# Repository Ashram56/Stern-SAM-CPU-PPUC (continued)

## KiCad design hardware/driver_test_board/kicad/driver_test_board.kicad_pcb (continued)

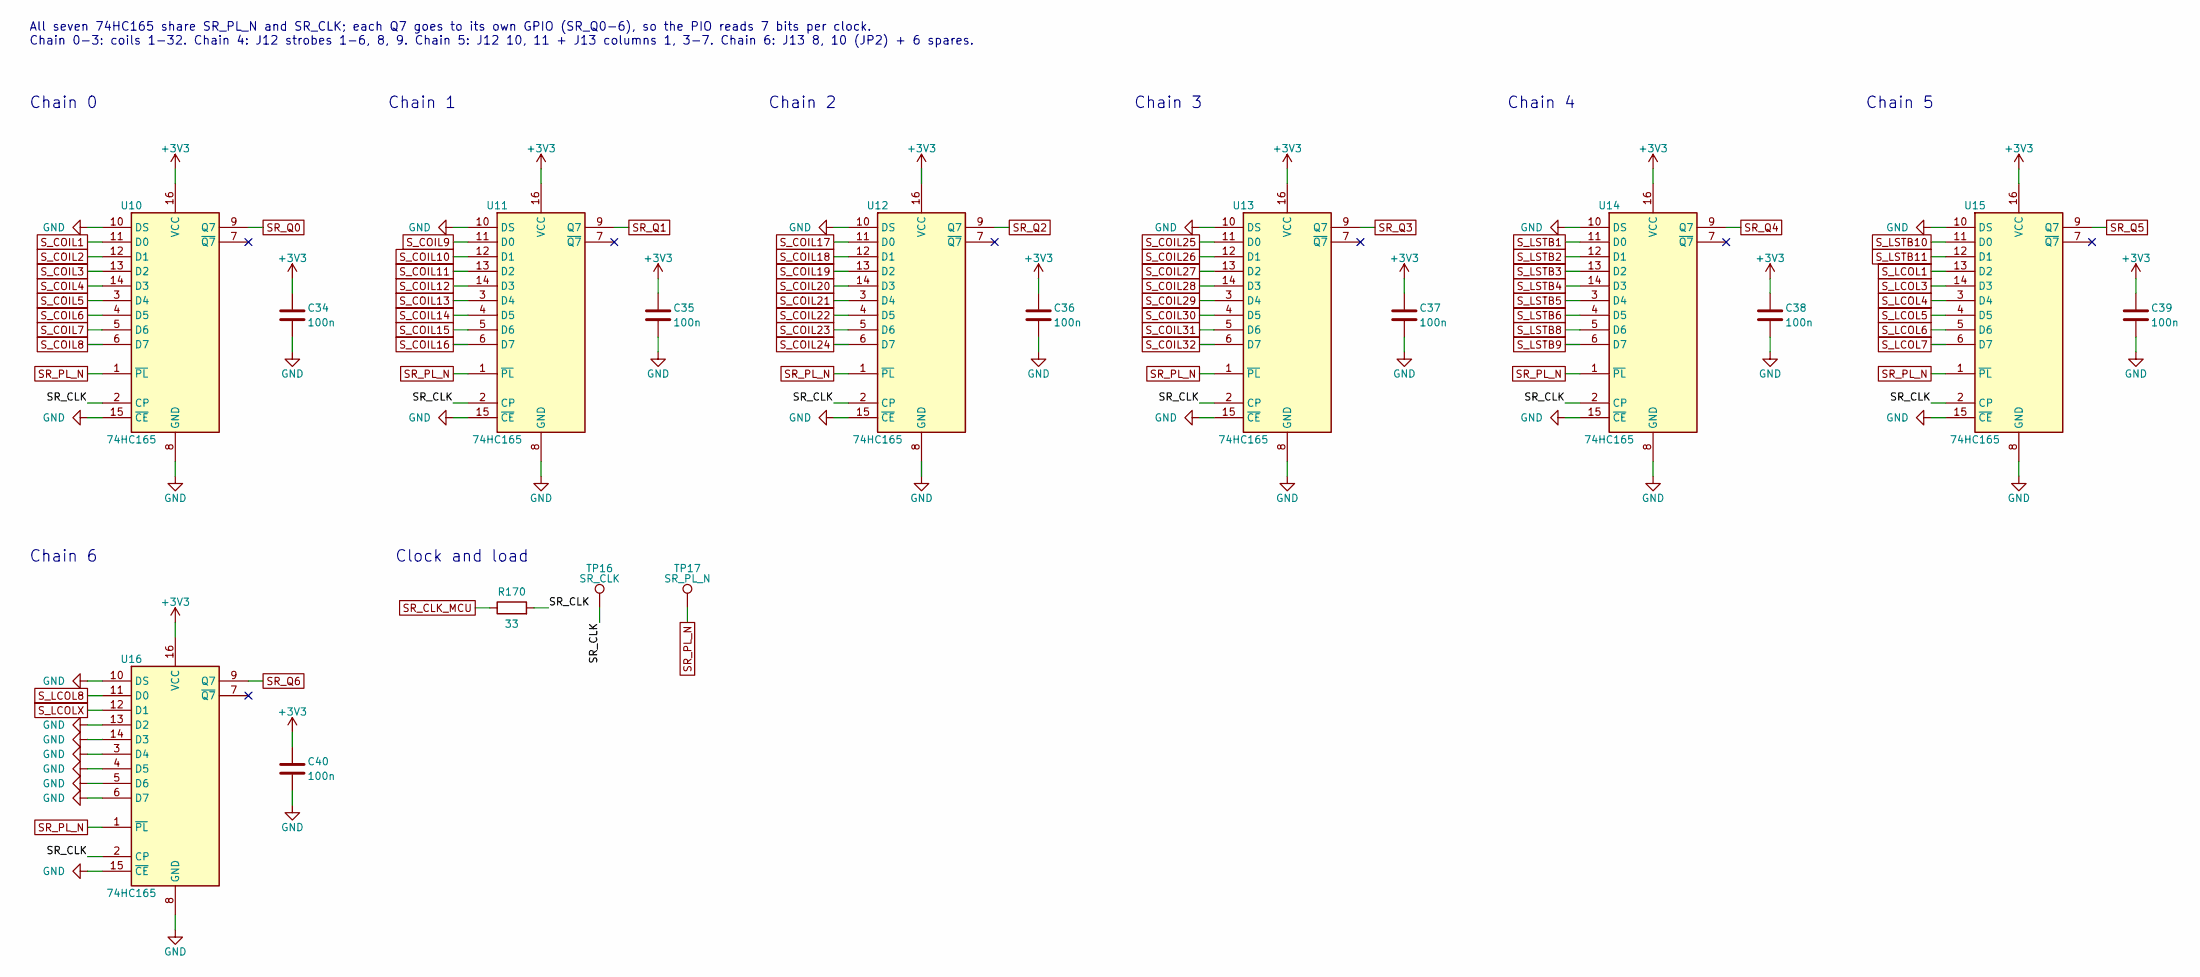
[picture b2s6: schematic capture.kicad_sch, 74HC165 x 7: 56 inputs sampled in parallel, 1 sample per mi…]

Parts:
C34, C35, C36, C37, C38, C39, C40: 100n; C_0805_2012Metric
R170: 33; R_0805_2012Metric
TP16: SR_CLK; TestPoint_Pad_D1.5mm
TP17: SR_PL_N; TestPoint_Pad_D1.5mm
U10, U11, U12, U13, U14, U15, U16: 74HC165; SOIC-16_3.9x9.9mm_P1.27mm

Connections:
+3V3: C34.1, C35.1, C36.1, C37.1, C38.1, C39.1, C40.1, U10.16 (VCC), U11.16 (VCC), U12.16 (VCC), U13.16 (VCC), U14.16 (VCC), U15.16 (VCC), U16.16 (VCC); also elsewhere on the board
/Capture/SR_CLK: R170.2, TP16.1, U10.2 (CP), U11.2 (CP), U12.2 (CP), U13.2 (CP), U14.2 (CP), U15.2 (CP), U16.2 (CP)
GND: C34.2, C35.2, C36.2, C37.2, C38.2, C39.2, C40.2, U10.8 (GND), U10.10 (DS), U10.15 (~CE), U11.8 (GND), U11.10 (DS), U11.15 (~CE), U12.8 (GND), U12.10 (DS), U12.15 (~CE), U13.8 (GND), U13.10 (DS), U13.15 (~CE), U14.8 (GND), U14.10 (DS), U14.15 (~CE), U15.8 (GND), U15.10 (DS), U15.15 (~CE), U16.3 (D4), U16.4 (D5), U16.5 (D6), U16.6 (D7), U16.8 (GND), U16.10 (DS), U16.13 (D2), U16.14 (D3), U16.15 (~CE); also elsewhere on the board
SR_CLK_MCU: R170.1; also elsewhere on the board
SR_PL_N: TP17.1, U10.1 (~PL), U11.1 (~PL), U12.1 (~PL), U13.1 (~PL), U14.1 (~PL), U15.1 (~PL), U16.1 (~PL); also elsewhere on the board
SR_Q0: U10.9 (Q7); also elsewhere on the board
SR_Q1: U11.9 (Q7); also elsewhere on the board
SR_Q2: U12.9 (Q7); also elsewhere on the board
SR_Q3: U13.9 (Q7); also elsewhere on the board
SR_Q4: U14.9 (Q7); also elsewhere on the board
SR_Q5: U15.9 (Q7); also elsewhere on the board
SR_Q6: U16.9 (Q7); also elsewhere on the board
S_COIL1: U10.11 (D0); also elsewhere on the board
S_COIL2: U10.12 (D1); also elsewhere on the board
S_COIL3: U10.13 (D2); also elsewhere on the board
S_COIL4: U10.14 (D3); also elsewhere on the board
S_COIL5: U10.3 (D4); also elsewhere on the board
S_COIL6: U10.4 (D5); also elsewhere on the board
S_COIL7: U10.5 (D6); also elsewhere on the board
S_COIL8: U10.6 (D7); also elsewhere on the board
S_COIL9: U11.11 (D0); also elsewhere on the board
S_COIL10: U11.12 (D1); also elsewhere on the board
S_COIL11: U11.13 (D2); also elsewhere on the board
S_COIL12: U11.14 (D3); also elsewhere on the board
S_COIL13: U11.3 (D4); also elsewhere on the board
S_COIL14: U11.4 (D5); also elsewhere on the board
S_COIL15: U11.5 (D6); also elsewhere on the board
S_COIL16: U11.6 (D7); also elsewhere on the board
S_COIL17: U12.11 (D0); also elsewhere on the board
S_COIL18: U12.12 (D1); also elsewhere on the board
S_COIL19: U12.13 (D2); also elsewhere on the board
S_COIL20: U12.14 (D3); also elsewhere on the board
S_COIL21: U12.3 (D4); also elsewhere on the board
S_COIL22: U12.4 (D5); also elsewhere on the board
S_COIL23: U12.5 (D6); also elsewhere on the board
S_COIL24: U12.6 (D7); also elsewhere on the board
S_COIL25: U13.11 (D0); also elsewhere on the board
S_COIL26: U13.12 (D1); also elsewhere on the board
S_COIL27: U13.13 (D2); also elsewhere on the board
S_COIL28: U13.14 (D3); also elsewhere on the board
S_COIL29: U13.3 (D4); also elsewhere on the board
S_COIL30: U13.4 (D5); also elsewhere on the board
S_COIL31: U13.5 (D6); also elsewhere on the board
S_COIL32: U13.6 (D7); also elsewhere on the board
S_LCOL1: U15.13 (D2); also elsewhere on the board
S_LCOL3: U15.14 (D3); also elsewhere on the board
S_LCOL4: U15.3 (D4); also elsewhere on the board
S_LCOL5: U15.4 (D5); also elsewhere on the board
S_LCOL6: U15.5 (D6); also elsewhere on the board
S_LCOL7: U15.6 (D7); also elsewhere on the board
S_LCOL8: U16.11 (D0); also elsewhere on the board
S_LCOLX: U16.12 (D1); also elsewhere on the board
S_LSTB1: U14.11 (D0); also elsewhere on the board
S_LSTB2: U14.12 (D1); also elsewhere on the board
S_LSTB3: U14.13 (D2); also elsewhere on the board
S_LSTB4: U14.14 (D3); also elsewhere on the board
S_LSTB5: U14.3 (D4); also elsewhere on the board
S_LSTB6: U14.4 (D5); also elsewhere on the board
S_LSTB8: U14.5 (D6); also elsewhere on the board
S_LSTB9: U14.6 (D7); also elsewhere on the board
S_LSTB10: U15.11 (D0); also elsewhere on the board
S_LSTB11: U15.12 (D1); also elsewhere on the board

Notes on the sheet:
All seven 74HC165 share SR_PL_N and SR_CLK; each Q7 goes to its own GPIO (SR_Q0-6), so the PIO reads 7 bits per clock. Chain 0-3: coils 1-32. Chain 4: J12 strobes 1-6, 8, 9. Chain 5: J12 10, 11 + J13 columns 1, 3-7. Chain 6: J13 8, 10 (JP2) + 6 spares.
Chain 0
Chain 1
Chain 2
Chain 3
Chain 4
Chain 5
Chain 6
Clock and load

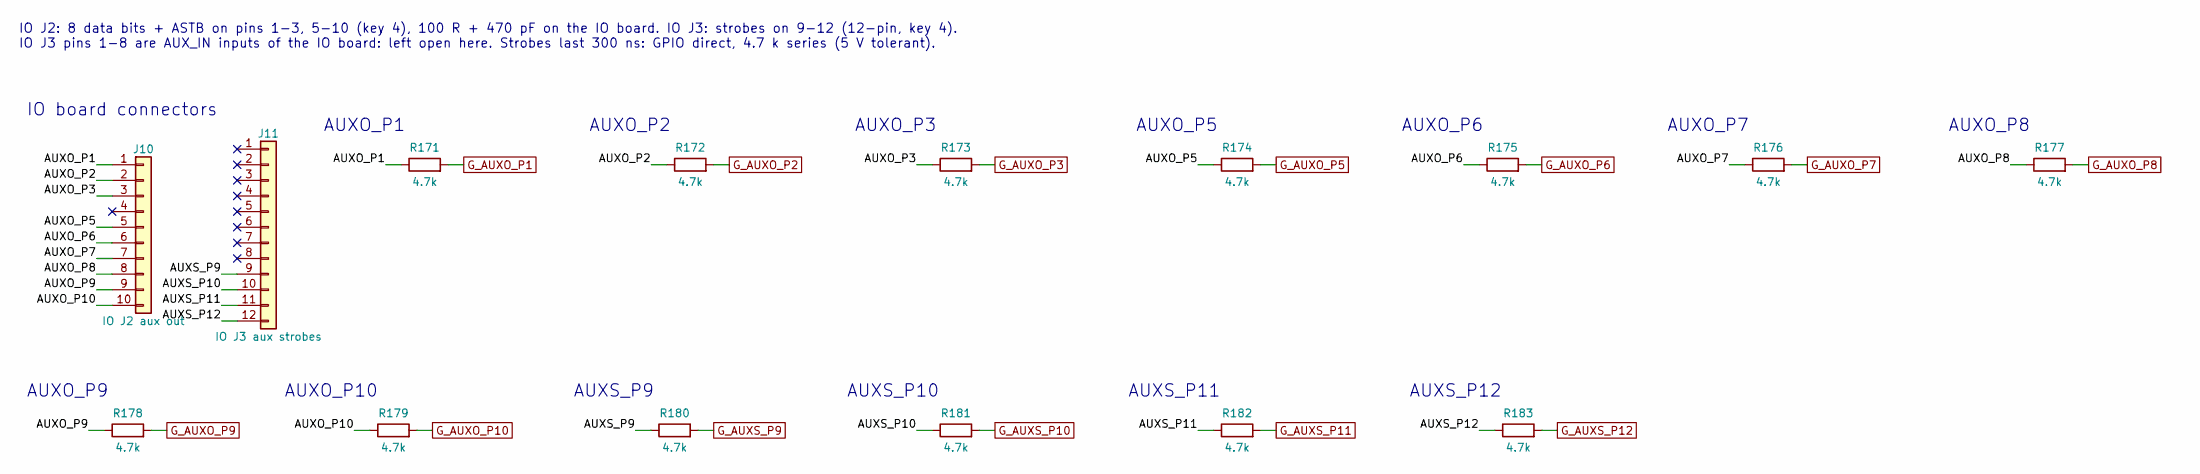
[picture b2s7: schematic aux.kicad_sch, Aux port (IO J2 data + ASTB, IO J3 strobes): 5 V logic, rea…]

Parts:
J10: IO J2 aux out; Molex_KK-396_A-41791-0010_1x10_P3.96mm_Vertical
J11: IO J3 aux strobes; Molex_KK-396_A-41791-0012_1x12_P3.96mm_Vertical
R171, R172, R173, R174, R175, R176, R177, R178, R179, R180, R181, R182, R183: 4.7k; R_0805_2012Metric

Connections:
/Aux port/AUXO_P1: J10.1, R171.1
/Aux port/AUXO_P2: J10.2, R172.1
/Aux port/AUXO_P3: J10.3, R173.1
/Aux port/AUXO_P5: J10.5, R174.1
/Aux port/AUXO_P6: J10.6, R175.1
/Aux port/AUXO_P7: J10.7, R176.1
/Aux port/AUXO_P8: J10.8, R177.1
/Aux port/AUXO_P9: J10.9, R178.1
/Aux port/AUXO_P10: J10.10, R179.1
/Aux port/AUXS_P9: J11.9, R180.1
/Aux port/AUXS_P10: J11.10, R181.1
/Aux port/AUXS_P11: J11.11, R182.1
/Aux port/AUXS_P12: J11.12, R183.1
G_AUXO_P1: R171.2; also elsewhere on the board
G_AUXO_P2: R172.2; also elsewhere on the board
G_AUXO_P3: R173.2; also elsewhere on the board
G_AUXO_P5: R174.2; also elsewhere on the board
G_AUXO_P6: R175.2; also elsewhere on the board
G_AUXO_P7: R176.2; also elsewhere on the board
G_AUXO_P8: R177.2; also elsewhere on the board
G_AUXO_P9: R178.2; also elsewhere on the board
G_AUXO_P10: R179.2; also elsewhere on the board
G_AUXS_P9: R180.2; also elsewhere on the board
G_AUXS_P10: R181.2; also elsewhere on the board
G_AUXS_P11: R182.2; also elsewhere on the board
G_AUXS_P12: R183.2; also elsewhere on the board

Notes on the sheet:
IO J2: 8 data bits + ASTB on pins 1-3, 5-10 (key 4), 100 R + 470 pF on the IO board. IO J3: strobes on 9-12 (12-pin, key 4). IO J3 pins 1-8 are AUX_IN inputs of the IO board: left open here. Strobes last 300 ns: GPIO direct, 4.7 k series (5 V tolerant).
IO board connectors
AUXO_P1
AUXO_P2
AUXO_P3
AUXO_P5
AUXO_P6
AUXO_P7
AUXO_P8
AUXO_P9
AUXO_P10
AUXS_P9
AUXS_P10
AUXS_P11
AUXS_P12

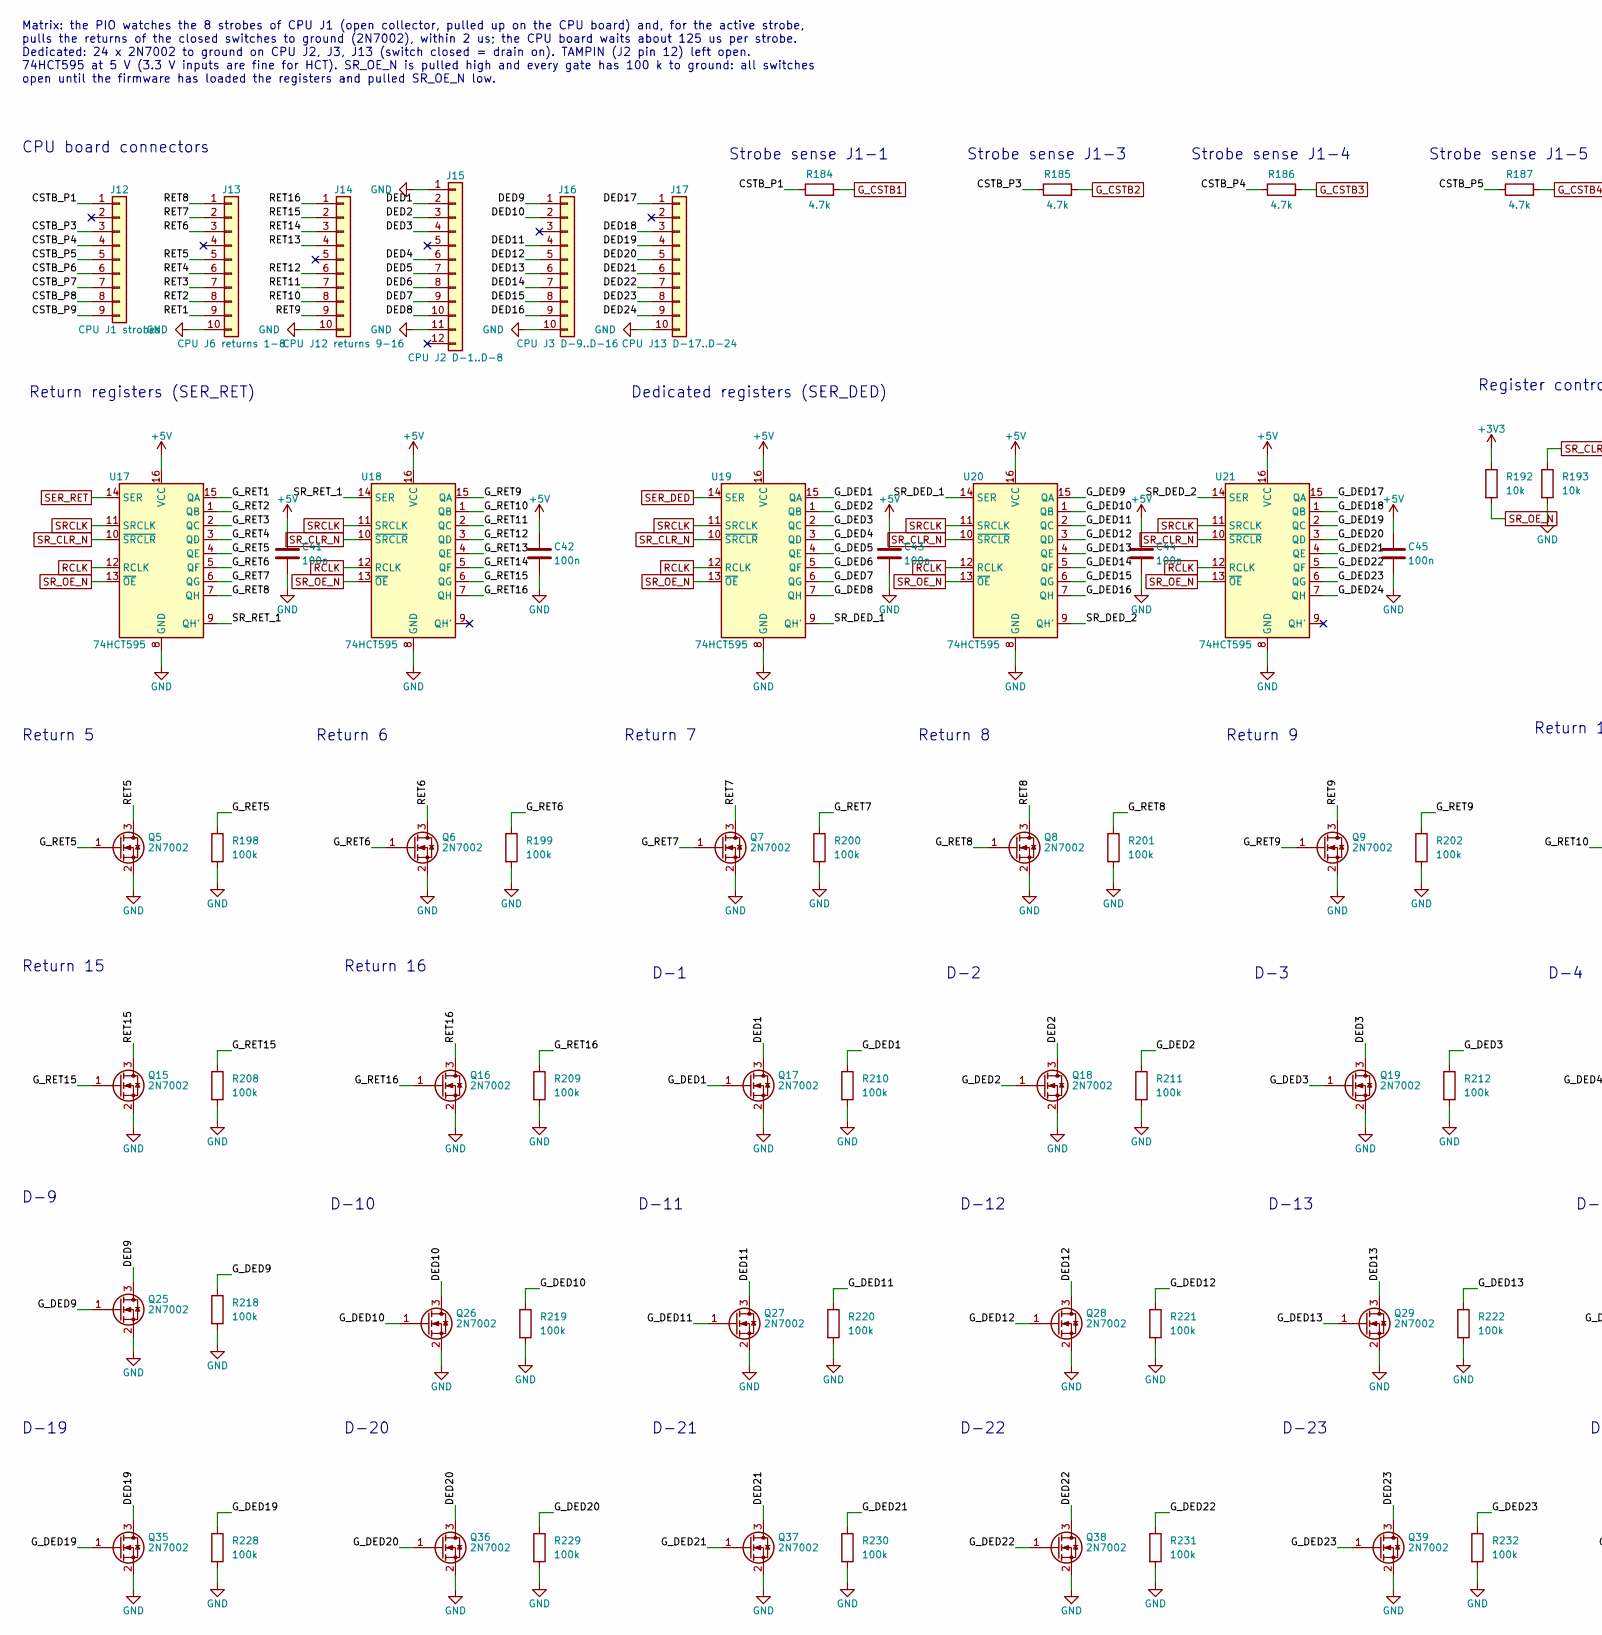
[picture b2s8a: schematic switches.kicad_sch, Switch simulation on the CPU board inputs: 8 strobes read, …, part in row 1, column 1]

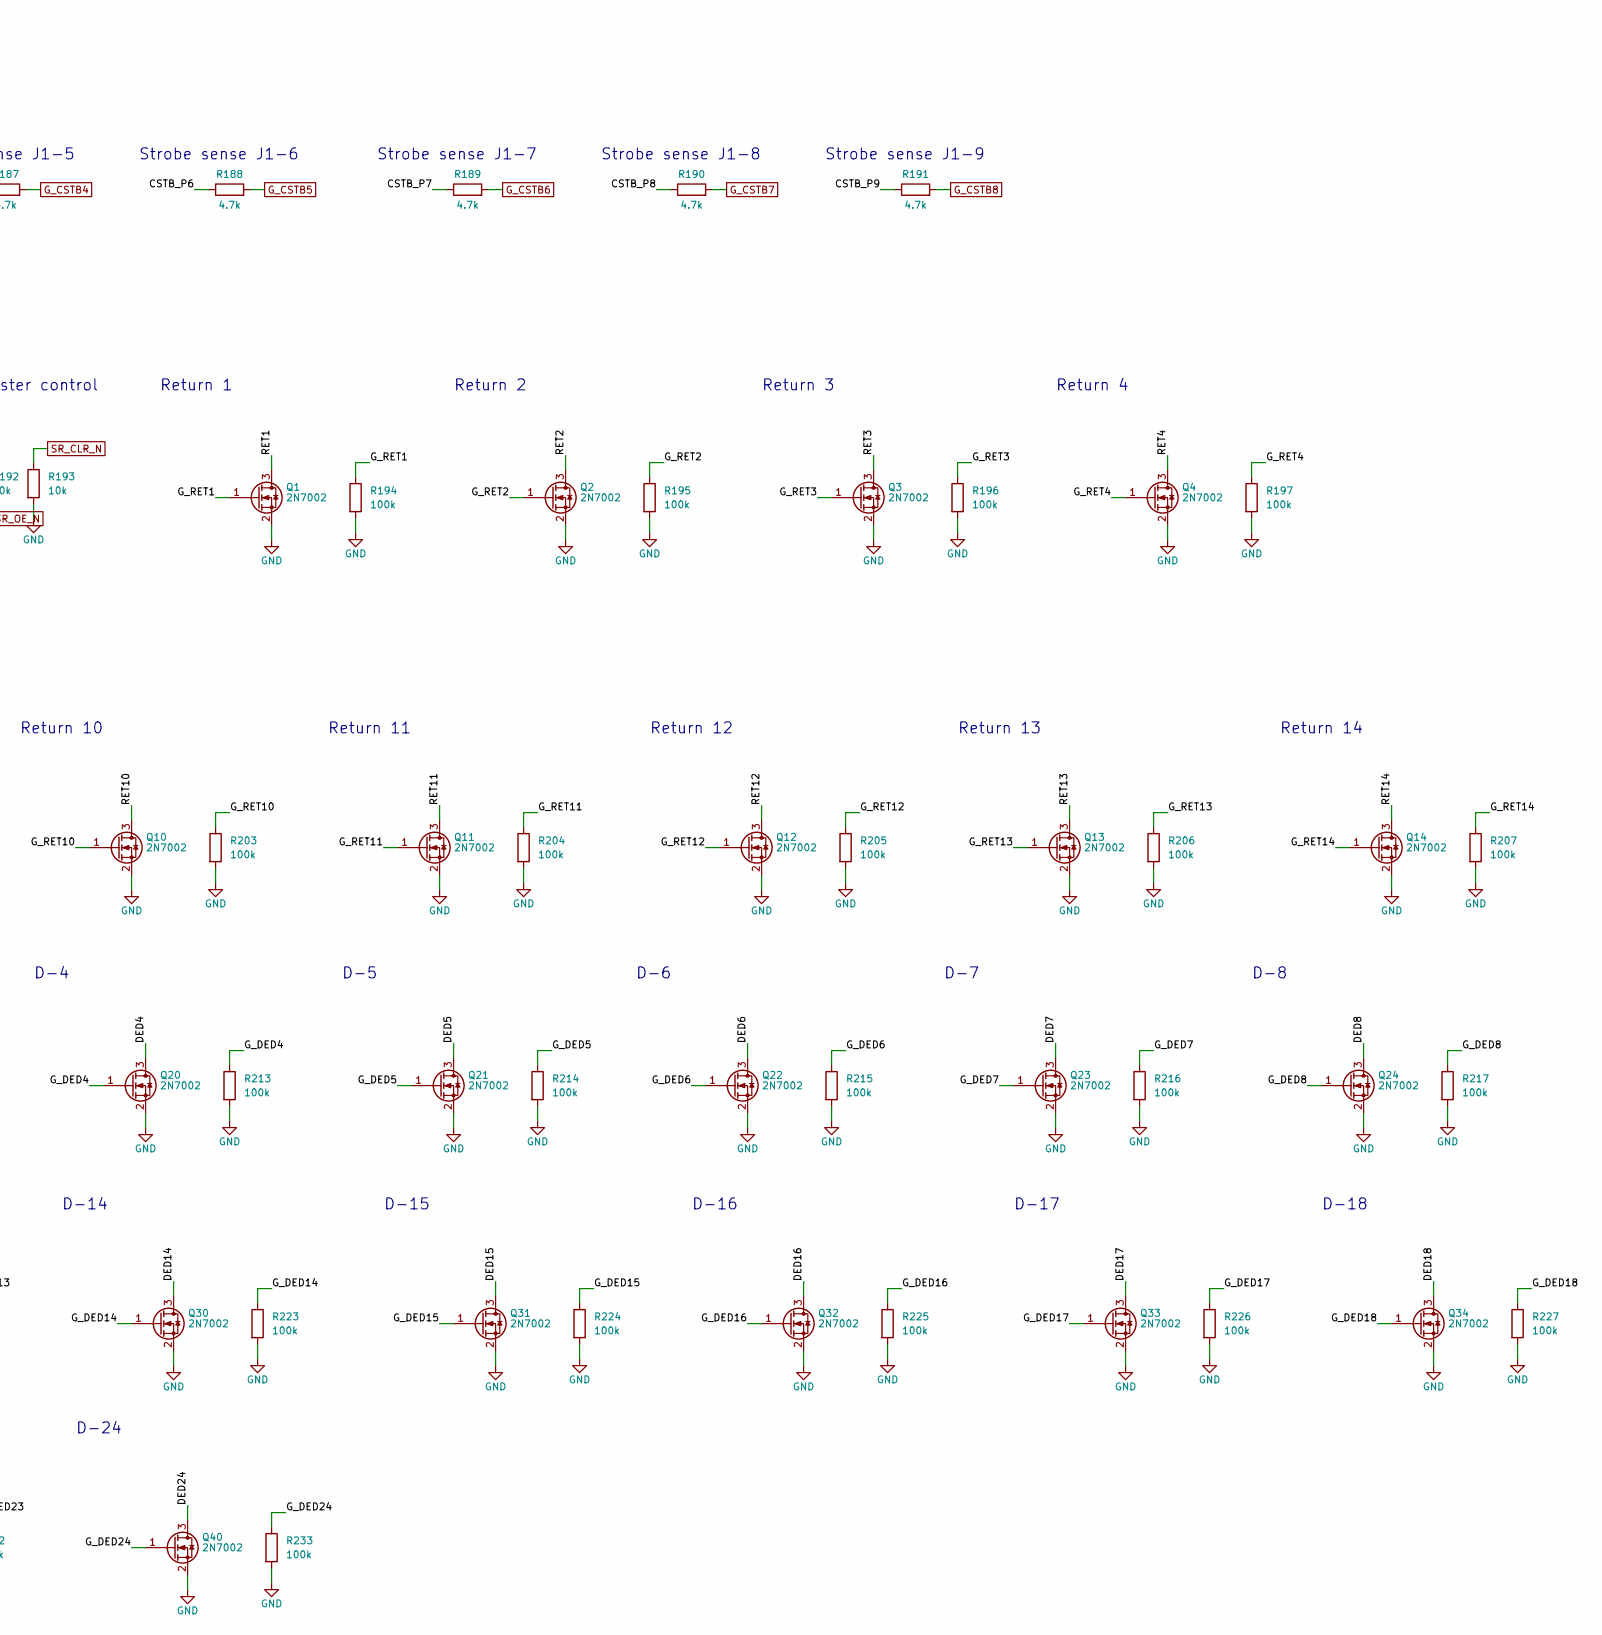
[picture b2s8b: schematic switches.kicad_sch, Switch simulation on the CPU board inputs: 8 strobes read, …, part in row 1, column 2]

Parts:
C41, C42, C43, C44, C45: 100n; C_0805_2012Metric
J12: CPU J1 strobes; Molex_KK-396_A-41791-0009_1x09_P3.96mm_Vertical
J13: CPU J6 returns 1-8; Molex_KK-396_A-41791-0010_1x10_P3.96mm_Vertical
J14: CPU J12 returns 9-16; Molex_KK-396_A-41791-0010_1x10_P3.96mm_Vertical
J15: CPU J2 D-1..D-8; Molex_KK-396_A-41791-0012_1x12_P3.96mm_Vertical
J16: CPU J3 D-9..D-16; Molex_KK-396_A-41791-0010_1x10_P3.96mm_Vertical
J17: CPU J13 D-17..D-24; Molex_KK-396_A-41791-0010_1x10_P3.96mm_Vertical
Q1, Q2, Q3, Q4, Q5, Q6, Q7, Q8, Q9, Q10, Q11, Q12, Q13, Q14, Q15, Q16, Q17, Q18, Q19, Q20, Q21, Q22, Q23, Q24, Q25, Q26, Q27, Q28, Q29, Q30, Q31, Q32, Q33, Q34, Q35, Q36, Q37, Q38, Q39, Q40: 2N7002; SOT-23
R184, R185, R186, R187, R188, R189, R190, R191: 4.7k; R_0805_2012Metric
R192, R193: 10k; R_0805_2012Metric
R194, R195, R196, R197, R198, R199, R200, R201, R202, R203, R204, R205, R206, R207, R208, R209, R210, R211, R212, R213, R214, R215, R216, R217, R218, R219, R220, R221, R222, R223, R224, R225, R226, R227, R228, R229, R230, R231, R232, R233: 100k; R_0805_2012Metric
U17, U18, U19, U20, U21: 74HCT595; SOIC-16_3.9x9.9mm_P1.27mm

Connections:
+3V3: R192.1; also elsewhere on the board
+5V: C41.1, C42.1, C43.1, C44.1, C45.1, U17.16 (VCC), U18.16 (VCC), U19.16 (VCC), U20.16 (VCC), U21.16 (VCC); also elsewhere on the board
/Switch simulation/CSTB_P1: J12.1, R184.1
/Switch simulation/CSTB_P3: J12.3, R185.1
/Switch simulation/CSTB_P4: J12.4, R186.1
/Switch simulation/CSTB_P5: J12.5, R187.1
/Switch simulation/CSTB_P6: J12.6, R188.1
/Switch simulation/CSTB_P7: J12.7, R189.1
/Switch simulation/CSTB_P8: J12.8, R190.1
/Switch simulation/CSTB_P9: J12.9, R191.1
/Switch simulation/DED1: J15.2, Q17.3 (D)
/Switch simulation/DED2: J15.3, Q18.3 (D)
/Switch simulation/DED3: J15.4, Q19.3 (D)
/Switch simulation/DED4: J15.6, Q20.3 (D)
/Switch simulation/DED5: J15.7, Q21.3 (D)
/Switch simulation/DED6: J15.8, Q22.3 (D)
/Switch simulation/DED7: J15.9, Q23.3 (D)
/Switch simulation/DED8: J15.10, Q24.3 (D)
/Switch simulation/DED9: J16.1, Q25.3 (D)
/Switch simulation/DED10: J16.2, Q26.3 (D)
/Switch simulation/DED11: J16.4, Q27.3 (D)
/Switch simulation/DED12: J16.5, Q28.3 (D)
/Switch simulation/DED13: J16.6, Q29.3 (D)
/Switch simulation/DED14: J16.7, Q30.3 (D)
/Switch simulation/DED15: J16.8, Q31.3 (D)
/Switch simulation/DED16: J16.9, Q32.3 (D)
/Switch simulation/DED17: J17.1, Q33.3 (D)
/Switch simulation/DED18: J17.3, Q34.3 (D)
/Switch simulation/DED19: J17.4, Q35.3 (D)
/Switch simulation/DED20: J17.5, Q36.3 (D)
/Switch simulation/DED21: J17.6, Q37.3 (D)
/Switch simulation/DED22: J17.7, Q38.3 (D)
/Switch simulation/DED23: J17.8, Q39.3 (D)
/Switch simulation/DED24: J17.9, Q40.3 (D)
/Switch simulation/G_DED1: Q17.1 (G), R210.1, U19.15 (QA)
/Switch simulation/G_DED2: Q18.1 (G), R211.1, U19.1 (QB)
/Switch simulation/G_DED3: Q19.1 (G), R212.1, U19.2 (QC)
/Switch simulation/G_DED4: Q20.1 (G), R213.1, U19.3 (QD)
/Switch simulation/G_DED5: Q21.1 (G), R214.1, U19.4 (QE)
/Switch simulation/G_DED6: Q22.1 (G), R215.1, U19.5 (QF)
/Switch simulation/G_DED7: Q23.1 (G), R216.1, U19.6 (QG)
/Switch simulation/G_DED8: Q24.1 (G), R217.1, U19.7 (QH)
/Switch simulation/G_DED9: Q25.1 (G), R218.1, U20.15 (QA)
/Switch simulation/G_DED10: Q26.1 (G), R219.1, U20.1 (QB)
/Switch simulation/G_DED11: Q27.1 (G), R220.1, U20.2 (QC)
/Switch simulation/G_DED12: Q28.1 (G), R221.1, U20.3 (QD)
/Switch simulation/G_DED13: Q29.1 (G), R222.1, U20.4 (QE)
/Switch simulation/G_DED14: Q30.1 (G), R223.1, U20.5 (QF)
/Switch simulation/G_DED15: Q31.1 (G), R224.1, U20.6 (QG)
/Switch simulation/G_DED16: Q32.1 (G), R225.1, U20.7 (QH)
/Switch simulation/G_DED17: Q33.1 (G), R226.1, U21.15 (QA)
/Switch simulation/G_DED18: Q34.1 (G), R227.1, U21.1 (QB)
/Switch simulation/G_DED19: Q35.1 (G), R228.1, U21.2 (QC)
/Switch simulation/G_DED20: Q36.1 (G), R229.1, U21.3 (QD)
/Switch simulation/G_DED21: Q37.1 (G), R230.1, U21.4 (QE)
/Switch simulation/G_DED22: Q38.1 (G), R231.1, U21.5 (QF)
/Switch simulation/G_DED23: Q39.1 (G), R232.1, U21.6 (QG)
/Switch simulation/G_DED24: Q40.1 (G), R233.1, U21.7 (QH)
/Switch simulation/G_RET1: Q1.1 (G), R194.1, U17.15 (QA)
/Switch simulation/G_RET2: Q2.1 (G), R195.1, U17.1 (QB)
/Switch simulation/G_RET3: Q3.1 (G), R196.1, U17.2 (QC)
/Switch simulation/G_RET4: Q4.1 (G), R197.1, U17.3 (QD)
/Switch simulation/G_RET5: Q5.1 (G), R198.1, U17.4 (QE)
/Switch simulation/G_RET6: Q6.1 (G), R199.1, U17.5 (QF)
/Switch simulation/G_RET7: Q7.1 (G), R200.1, U17.6 (QG)
/Switch simulation/G_RET8: Q8.1 (G), R201.1, U17.7 (QH)
/Switch simulation/G_RET9: Q9.1 (G), R202.1, U18.15 (QA)
/Switch simulation/G_RET10: Q10.1 (G), R203.1, U18.1 (QB)
/Switch simulation/G_RET11: Q11.1 (G), R204.1, U18.2 (QC)
/Switch simulation/G_RET12: Q12.1 (G), R205.1, U18.3 (QD)
/Switch simulation/G_RET13: Q13.1 (G), R206.1, U18.4 (QE)
/Switch simulation/G_RET14: Q14.1 (G), R207.1, U18.5 (QF)
/Switch simulation/G_RET15: Q15.1 (G), R208.1, U18.6 (QG)
/Switch simulation/G_RET16: Q16.1 (G), R209.1, U18.7 (QH)
/Switch simulation/RET1: J13.9, Q1.3 (D)
/Switch simulation/RET2: J13.8, Q2.3 (D)
/Switch simulation/RET3: J13.7, Q3.3 (D)
/Switch simulation/RET4: J13.6, Q4.3 (D)
/Switch simulation/RET5: J13.5, Q5.3 (D)
/Switch simulation/RET6: J13.3, Q6.3 (D)
/Switch simulation/RET7: J13.2, Q7.3 (D)
/Switch simulation/RET8: J13.1, Q8.3 (D)
/Switch simulation/RET9: J14.9, Q9.3 (D)
/Switch simulation/RET10: J14.8, Q10.3 (D)
/Switch simulation/RET11: J14.7, Q11.3 (D)
/Switch simulation/RET12: J14.6, Q12.3 (D)
/Switch simulation/RET13: J14.4, Q13.3 (D)
/Switch simulation/RET14: J14.3, Q14.3 (D)
/Switch simulation/RET15: J14.2, Q15.3 (D)
/Switch simulation/RET16: J14.1, Q16.3 (D)
/Switch simulation/SR_DED_1: U19.9 (QH'), U20.14 (SER)
/Switch simulation/SR_DED_2: U20.9 (QH'), U21.14 (SER)
/Switch simulation/SR_RET_1: U17.9 (QH'), U18.14 (SER)
GND: C41.2, C42.2, C43.2, C44.2, C45.2, J13.10, J14.10, J15.1, J15.11, J16.10, J17.10, Q1.2 (S), Q2.2 (S), Q3.2 (S), Q4.2 (S), Q5.2 (S), Q6.2 (S), Q7.2 (S), Q8.2 (S), Q9.2 (S), Q10.2 (S), Q11.2 (S), Q12.2 (S), Q13.2 (S), Q14.2 (S), Q15.2 (S), Q16.2 (S), Q17.2 (S), Q18.2 (S), Q19.2 (S), Q20.2 (S), Q21.2 (S), Q22.2 (S), Q23.2 (S), Q24.2 (S), Q25.2 (S), Q26.2 (S), Q27.2 (S), Q28.2 (S), Q29.2 (S), Q30.2 (S), Q31.2 (S), Q32.2 (S), Q33.2 (S), Q34.2 (S), Q35.2 (S), Q36.2 (S), Q37.2 (S), Q38.2 (S), Q39.2 (S), Q40.2 (S), R193.2, R194.2, R195.2, R196.2, R197.2, R198.2, R199.2, R200.2, R201.2, R202.2, R203.2, R204.2, R205.2, R206.2, R207.2, R208.2, R209.2, R210.2, R211.2, R212.2, R213.2, R214.2, R215.2, R216.2, R217.2, R218.2, R219.2, R220.2, R221.2, R222.2, R223.2, R224.2, R225.2, R226.2, R227.2, R228.2, R229.2, R230.2, R231.2, R232.2, R233.2, U17.8 (GND), U18.8 (GND), U19.8 (GND), U20.8 (GND), U21.8 (GND); also elsewhere on the board
G_CSTB1: R184.2; also elsewhere on the board
G_CSTB2: R185.2; also elsewhere on the board
G_CSTB3: R186.2; also elsewhere on the board
G_CSTB4: R187.2; also elsewhere on the board
G_CSTB5: R188.2; also elsewhere on the board
G_CSTB6: R189.2; also elsewhere on the board
G_CSTB7: R190.2; also elsewhere on the board
G_CSTB8: R191.2; also elsewhere on the board
RCLK: U17.12 (RCLK), U18.12 (RCLK), U19.12 (RCLK), U20.12 (RCLK), U21.12 (RCLK); also elsewhere on the board
SER_DED: U19.14 (SER); also elsewhere on the board
SER_RET: U17.14 (SER); also elsewhere on the board
SRCLK: U17.11 (SRCLK), U18.11 (SRCLK), U19.11 (SRCLK), U20.11 (SRCLK), U21.11 (SRCLK); also elsewhere on the board
SR_CLR_N: R193.1, U17.10 (~SRCLR), U18.10 (~SRCLR), U19.10 (~SRCLR), U20.10 (~SRCLR), U21.10 (~SRCLR); also elsewhere on the board
SR_OE_N: R192.2, U17.13 (~OE), U18.13 (~OE), U19.13 (~OE), U20.13 (~OE), U21.13 (~OE); also elsewhere on the board

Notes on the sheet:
Matrix: the PIO watches the 8 strobes of CPU J1 (open collector, pulled up on the CPU board) and, for the active strobe, pulls the returns of the closed switches to ground (2N7002), within 2 us; the CPU board waits about 125 us per strobe. Dedicated: 24 x 2N7002 to ground on CPU J2, J3, J13 (switch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
CPU board connectors
Strobe sense J1-1
Strobe sense J1-3
Strobe sense J1-4
Strobe sense J1-5
Strobe sense J1-6
Strobe sense J1-7
Strobe sense J1-8
Strobe sense J1-9
Return registers (SER_RET)
Dedicated registers (SER_DED)
Register control
Return 1
Return 2
Return 3
Return 4
Return 5
Return 6
Return 7
Return 8
Return 9
Return 10
Return 11
Return 12
Return 13
Return 14
Return 15
Return 16
D-1
D-2
D-3
D-4
D-5
D-6
D-7
D-8
D-9
D-10
D-11

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
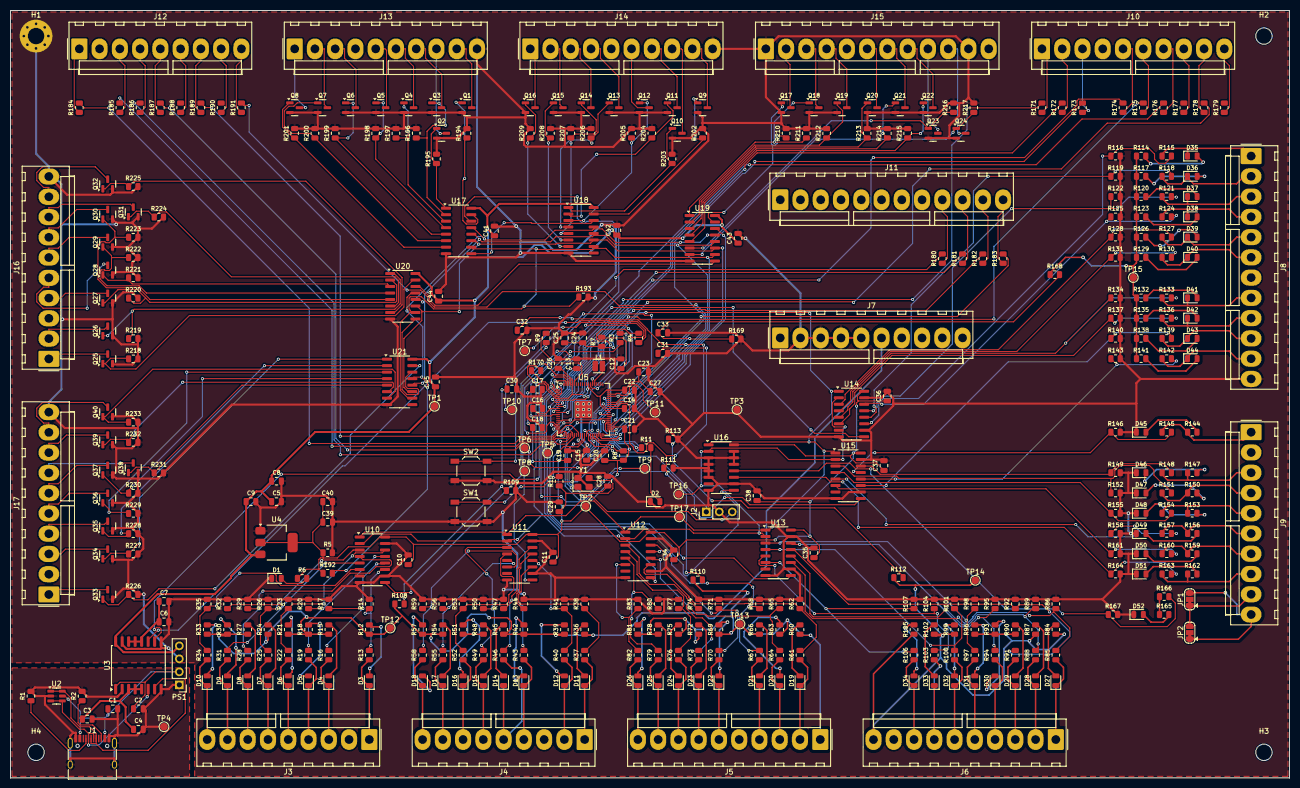
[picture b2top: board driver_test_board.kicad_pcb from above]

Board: 2 copper layers, 250.0 x 150.0 mm, 431 parts (0 on the bottom side), 337 nets.

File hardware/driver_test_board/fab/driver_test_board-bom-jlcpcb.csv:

Comment,Designator,Footprint,LCSC Part #
10u,"C1,C8,C9,C10",C_0805_2012Metric,C15850
100n,"C2,C4,C5,C7,C11,C14,C15,C16,C18,C19,C20,C21,C22,C23,C24,C25,C26,C27,C30,C31,C32,C33,C34,C35,C36,C37,C38,C39,C40,C41,C42,C43,C44,C45",C_0805_2012Metric,C49678
1u,"C3,C6",C_0805_2012Metric,C28323
4.7u,"C12,C13,C17",C_0805_2012Metric,C1779
15p,"C28,C29",C_0805_2012Metric,C63339
green,D1,LED_0805_2012Metric,C2297
yellow,"D2,D45,D46,D47,D48,D49,D50,D51,D52",LED_0805_2012Metric,C2296
red,"D3,D4,D5,D6,D7,D8,D9,D10,D11,D12,D13,D14,D15,D16,D17,D18,D19,D20,D21,D22,D23,D24,D25,D26,D27,D28,D29,D30,D31,D32,D33,D34,D35,D36,D37,D38,D39,D40,D41,D42,D43,D44",LED_0805_2012Metric,C84256
USB-C,J1,USB_C_Receptacle_HRO_TYPE-C-31-M-12,C165948
3.3u,L1,L_Cenker_CKCS201610,C167673
B0505S-1WR3,PS1,PinHeader_1x04_P2.54mm_Vertical,C2992394
2N7002,"Q1,Q2,Q3,Q4,Q5,Q6,Q7,Q8,Q9,Q10,Q11,Q12,Q13,Q14,Q15,Q16,Q17,Q18,Q19,Q20,Q21,Q22,Q23,Q24,Q25,Q26,Q27,Q28,Q29,Q30,Q31,Q32,Q33,Q34,Q35,Q36,Q37,Q38,Q39,Q40",SOT-23,C8545
5.1k,"R1,R2",R_0805_2012Metric,C27834
27,"R3,R4",R_0805_2012Metric,C17594
330,R5,R_0805_2012Metric,C17630
1k,"R6,R9,R10,R11",R_0805_2012Metric,C17513
33,"R7,R170",R_0805_2012Metric,C17634
10k,"R8,R144,R147,R150,R153,R156,R159,R162,R165,R192,R193",R_0805_2012Metric,C17414
47k,"R12,R14,R15,R17,R18,R20,R21,R23,R24,R26,R27,R29,R30,R32,R33,R35,R36,R38,R39,R41,R42,R44,R45,R47,R48,R50,R51,R53,R54,R56,R57,R59,R62,R65,R68,R71,R74,R77,R80,R83,R86,R89,R92,R95,R98,R101,R104,R107,R116,R119,R122,R125,R128,R131,R134,R137,R140,R143,R146,R149,R152,R155,R158,R161,R164,R167",R_0805_2012Metric,C17713
220k,"R13,R16,R19,R22,R25,R28,R31,R34,R37,R40,R43,R46,R49,R52,R55,R58,R61,R64,R67,R70,R73,R76,R79,R82,R85,R88,R91,R94,R97,R100,R103,R106,R115,R118,R121,R124,R127,R130,R133,R136,R139,R142,R145,R148,R151,R154,R157,R160,R163,R166",R_0805_2012Metric,C17556
22k,"R60,R63,R66,R69,R72,R75,R78,R81,R84,R87,R90,R93,R96,R99,R102,R105,R114,R117,R120,R123,R126,R129,R132,R135,R138,R141",R_0805_2012Metric,C17560
100k,"R108,R110,R112,R168,R194,R195,R196,R197,R198,R199,R200,R201,R202,R203,R204,R205,R206,R207,R208,R209,R210,R211,R212,R213,R214,R215,R216,R217,R218,R219,R220,R221,R222,R223,R224,R225,R226,R227,R228,R229,R230,R231,R232,R233",R_0805_2012Metric,C149504
4.7k,"R109,R111,R113,R169,R171,R172,R173,R174,R175,R176,R177,R178,R179,R180,R181,R182,R183,R184,R185,R186,R187,R188,R189,R190,R191",R_0805_2012Metric,C17673
RESET,SW1,SW_SPST_TL3342,C29780122
BOOTSEL,SW2,SW_SPST_TL3342,C29780122
USBLC6-2SC6,U2,SOT-23-6,C7519
ADuM3160BRWZ,U3,SOIC-16W_7.5x10.3mm_P1.27mm,C284149
NCP1117-3.3,U4,SOT-223-3_TabPin2,C26537
RP2354B,U5,QFN-80-1EP_10x10mm_P0.4mm_EP3.4x3.4mm,C39843328
74HC165,"U10,U11,U12,U13,U14,U15,U16",SOIC-16_3.9x9.9mm_P1.27mm,C5613
74HCT595,"U17,U18,U19,U20,U21",SOIC-16_3.9x9.9mm_P1.27mm,C282339
12MHz,Y1,Crystal_SMD_3225-4Pin_3.2x2.5mm,C133337
